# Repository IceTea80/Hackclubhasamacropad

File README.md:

My name is Hasan Siddiq and I created a 16 key macropad with a rotary encoder. I made this hackpad so when I game I can have a smaller keyboard or have hotkeys set for when I stream for sound effects or to control my mic.

Making this macropad let me use Fusion 360 and KiCad for the first time. It let me learn new skills and get experience in programs that will be useful for projects in the future.

PCB:

schematic:

Final product/case:

BOM:
16 cherry mx switches
RP240
17 diodes
one rotary encoder
40$ for pcb
case filament 30$

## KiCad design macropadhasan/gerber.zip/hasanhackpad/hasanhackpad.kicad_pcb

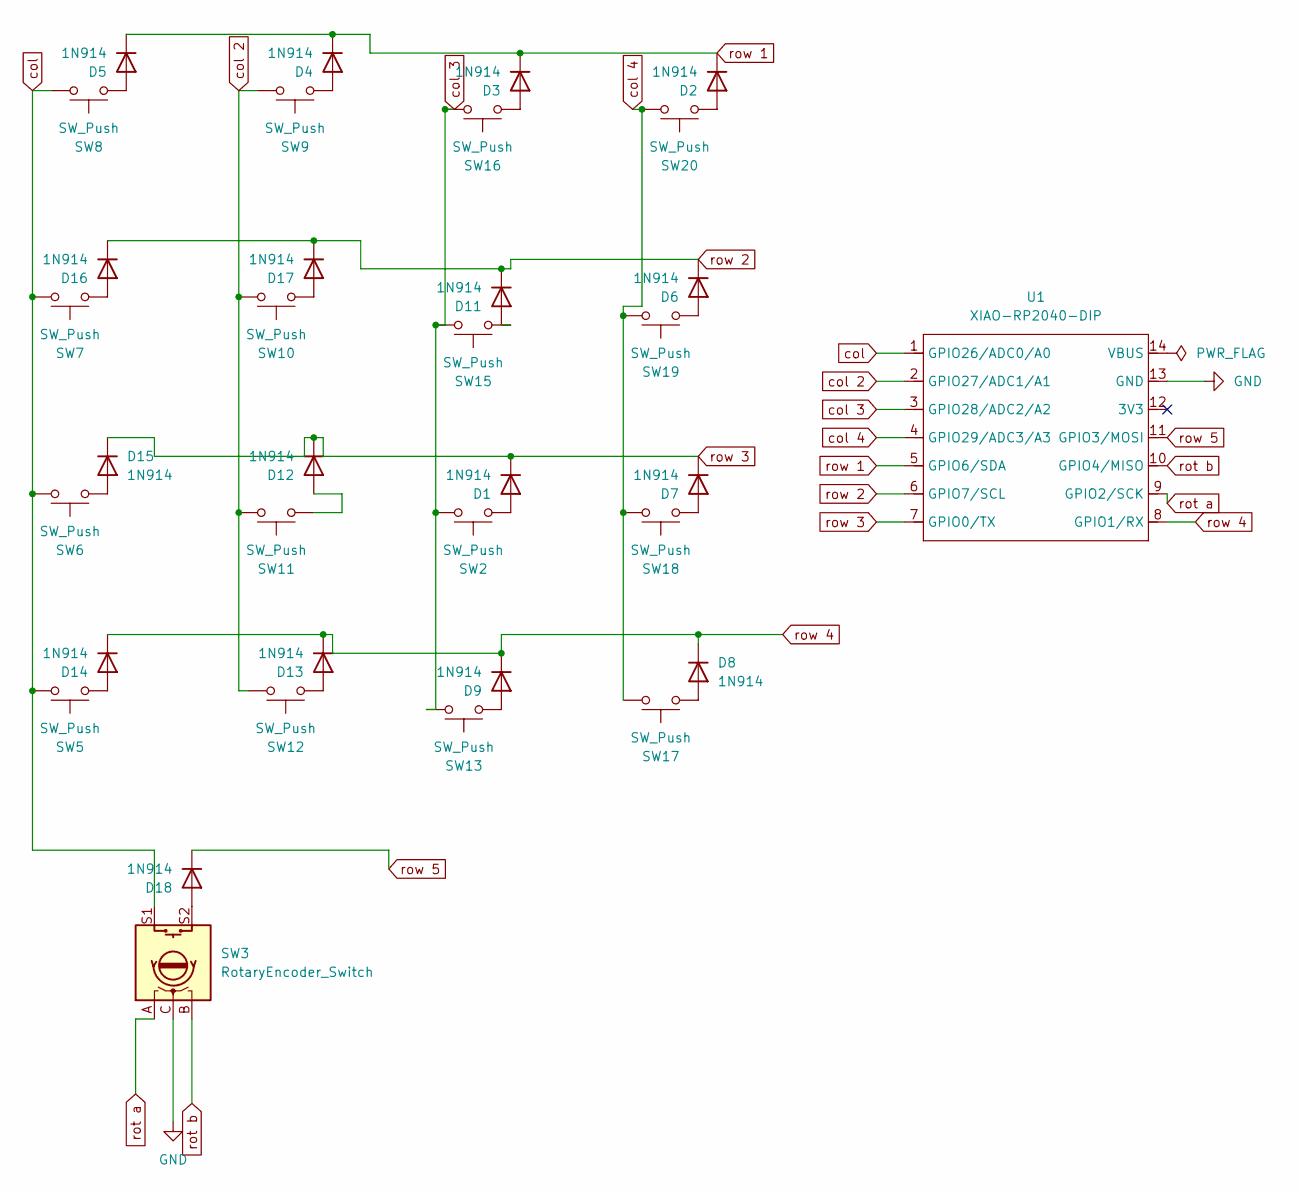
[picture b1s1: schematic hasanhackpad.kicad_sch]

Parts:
D1, D2, D3, D4, D5, D6, D7, D8, D9, D11, D12, D13, D14, D15, D16, D17, D18: 1N914; D_DO-35_SOD27_P7.62mm_Horizontal
SW2, SW5, SW6, SW7, SW8, SW9, SW10, SW11, SW12, SW13, SW15, SW16, SW17, SW18, SW19, SW20: SW_Push; SW_Cherry_MX_1.00u_PCB
SW3: RotaryEncoder_Switch; RotaryEncoder_Alps_EC11E-Switch_Vertical_H20mm
U1: XIAO-RP2040-DIP

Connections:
+5V: U1.14 (VBUS)
unnamed: D1.2 (A), SW2.1
unnamed: D2.2 (A), SW20.1
unnamed: D3.2 (A), SW16.1
unnamed: D4.2 (A), SW9.1
unnamed: D5.2 (A), SW8.1
unnamed: D6.2 (A), SW19.1
unnamed: D7.2 (A), SW18.1
unnamed: D8.2 (A), SW17.1
unnamed: D9.2 (A), SW13.1
unnamed: D11.2 (A), SW15.1
unnamed: D12.2 (A), SW11.1
unnamed: D13.2 (A), SW12.1
unnamed: D14.2 (A), SW5.1
unnamed: D15.2 (A), SW6.1
unnamed: D16.2 (A), SW7.1
unnamed: D17.2 (A), SW10.1
unnamed: D18.2 (A), SW3.S2
col: SW3.S1, SW5.2, SW6.2, SW7.2, SW8.2, U1.1 (GPIO26/ADC0/A0)
col 2: SW9.2, SW10.2, SW11.2, SW12.2, U1.2 (GPIO27/ADC1/A1)
col 3: SW2.2, SW13.2, SW15.2, SW16.2, U1.3 (GPIO28/ADC2/A2)
col 4: SW17.2, SW18.2, SW19.2, SW20.2, U1.4 (GPIO29/ADC3/A3)
rot a: SW3.A, U1.9 (GPIO2/SCK)
rot b: SW3.B, U1.10 (GPIO4/MISO)
rot c: SW3.C, U1.13 (GND)
row 1: D2.1 (K), D3.1 (K), D4.1 (K), D5.1 (K), U1.5 (GPIO6/SDA)
row 2: D6.1 (K), D11.1 (K), D16.1 (K), D17.1 (K), U1.6 (GPIO7/SCL)
row 3: D1.1 (K), D7.1 (K), D12.1 (K), D15.1 (K), U1.7 (GPIO0/TX)

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
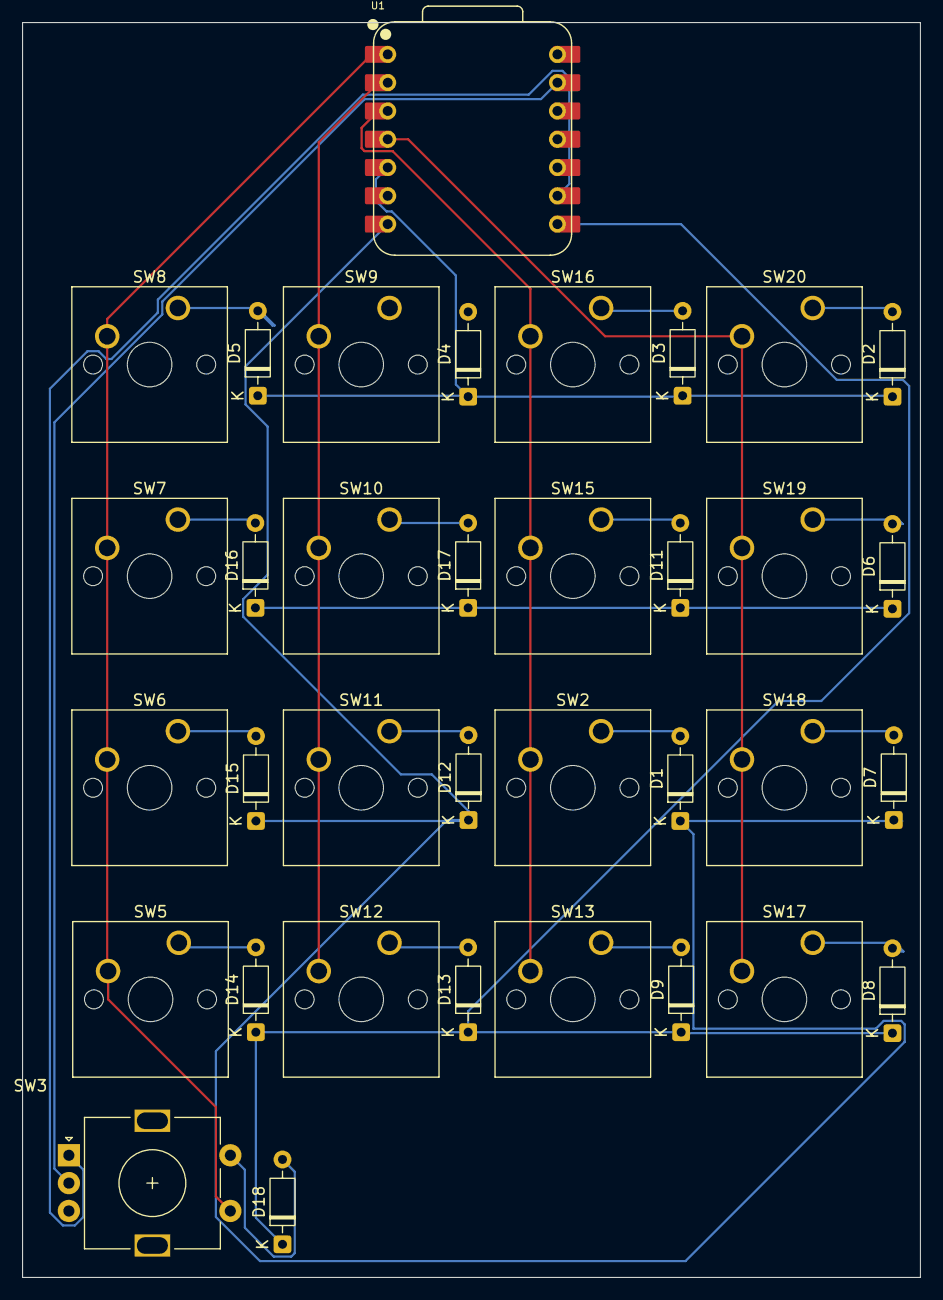
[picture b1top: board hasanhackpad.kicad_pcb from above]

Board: 2 copper layers, 80.6 x 112.7 mm, 35 parts (0 on the bottom side), 28 nets.
